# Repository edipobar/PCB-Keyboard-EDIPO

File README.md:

# PCB-Keyboard-EDIPO
Custom Keyboard PCB

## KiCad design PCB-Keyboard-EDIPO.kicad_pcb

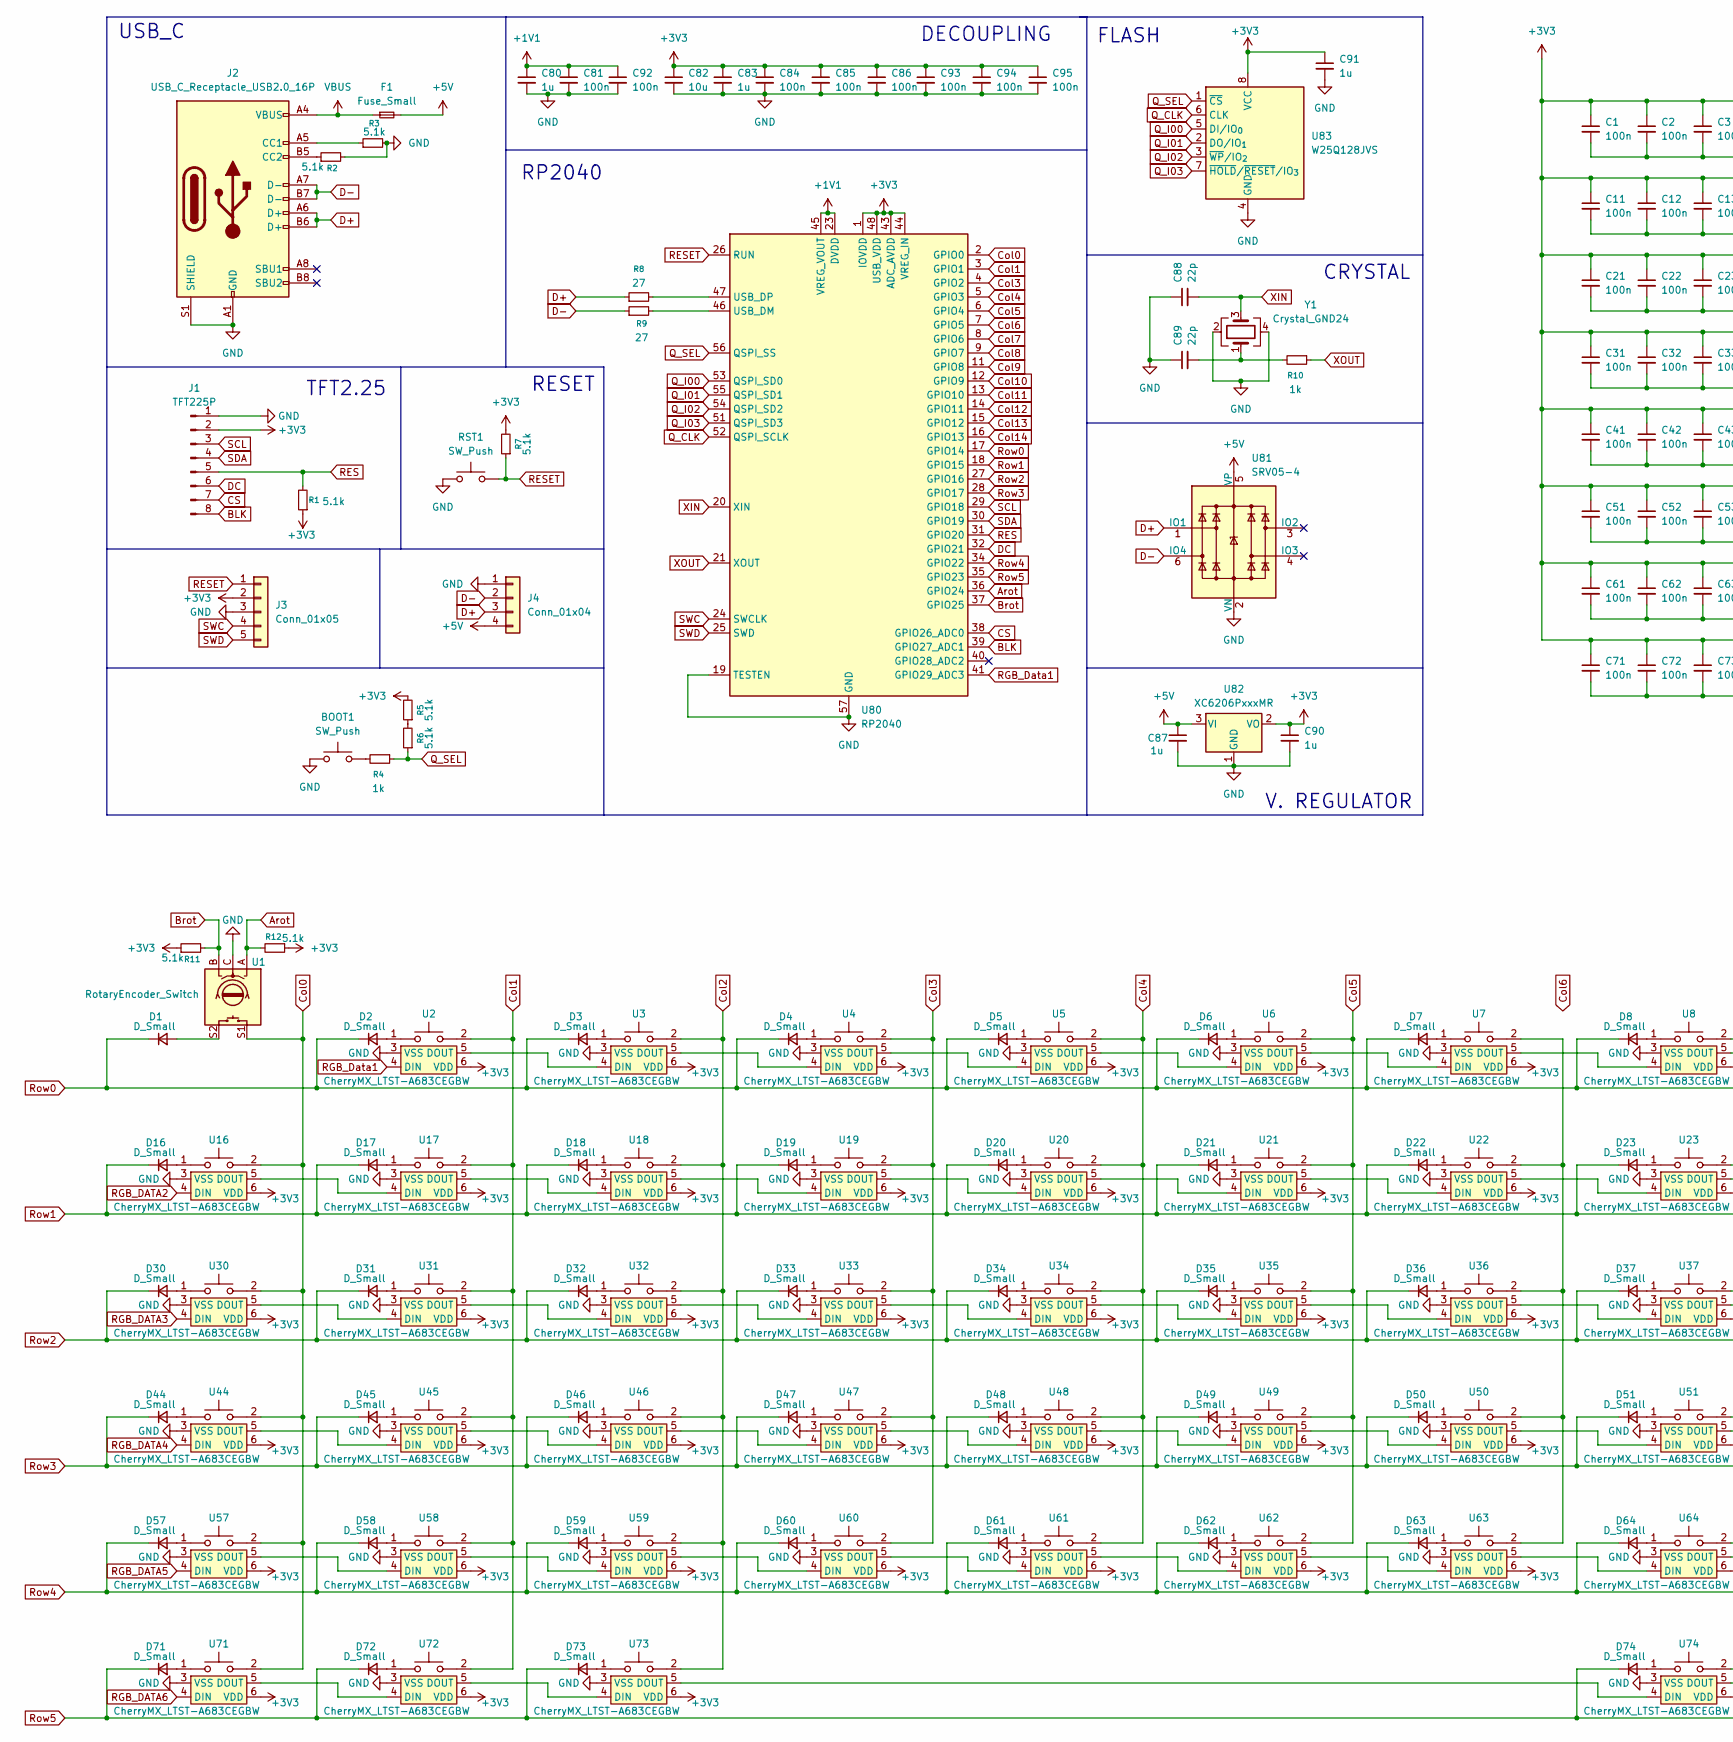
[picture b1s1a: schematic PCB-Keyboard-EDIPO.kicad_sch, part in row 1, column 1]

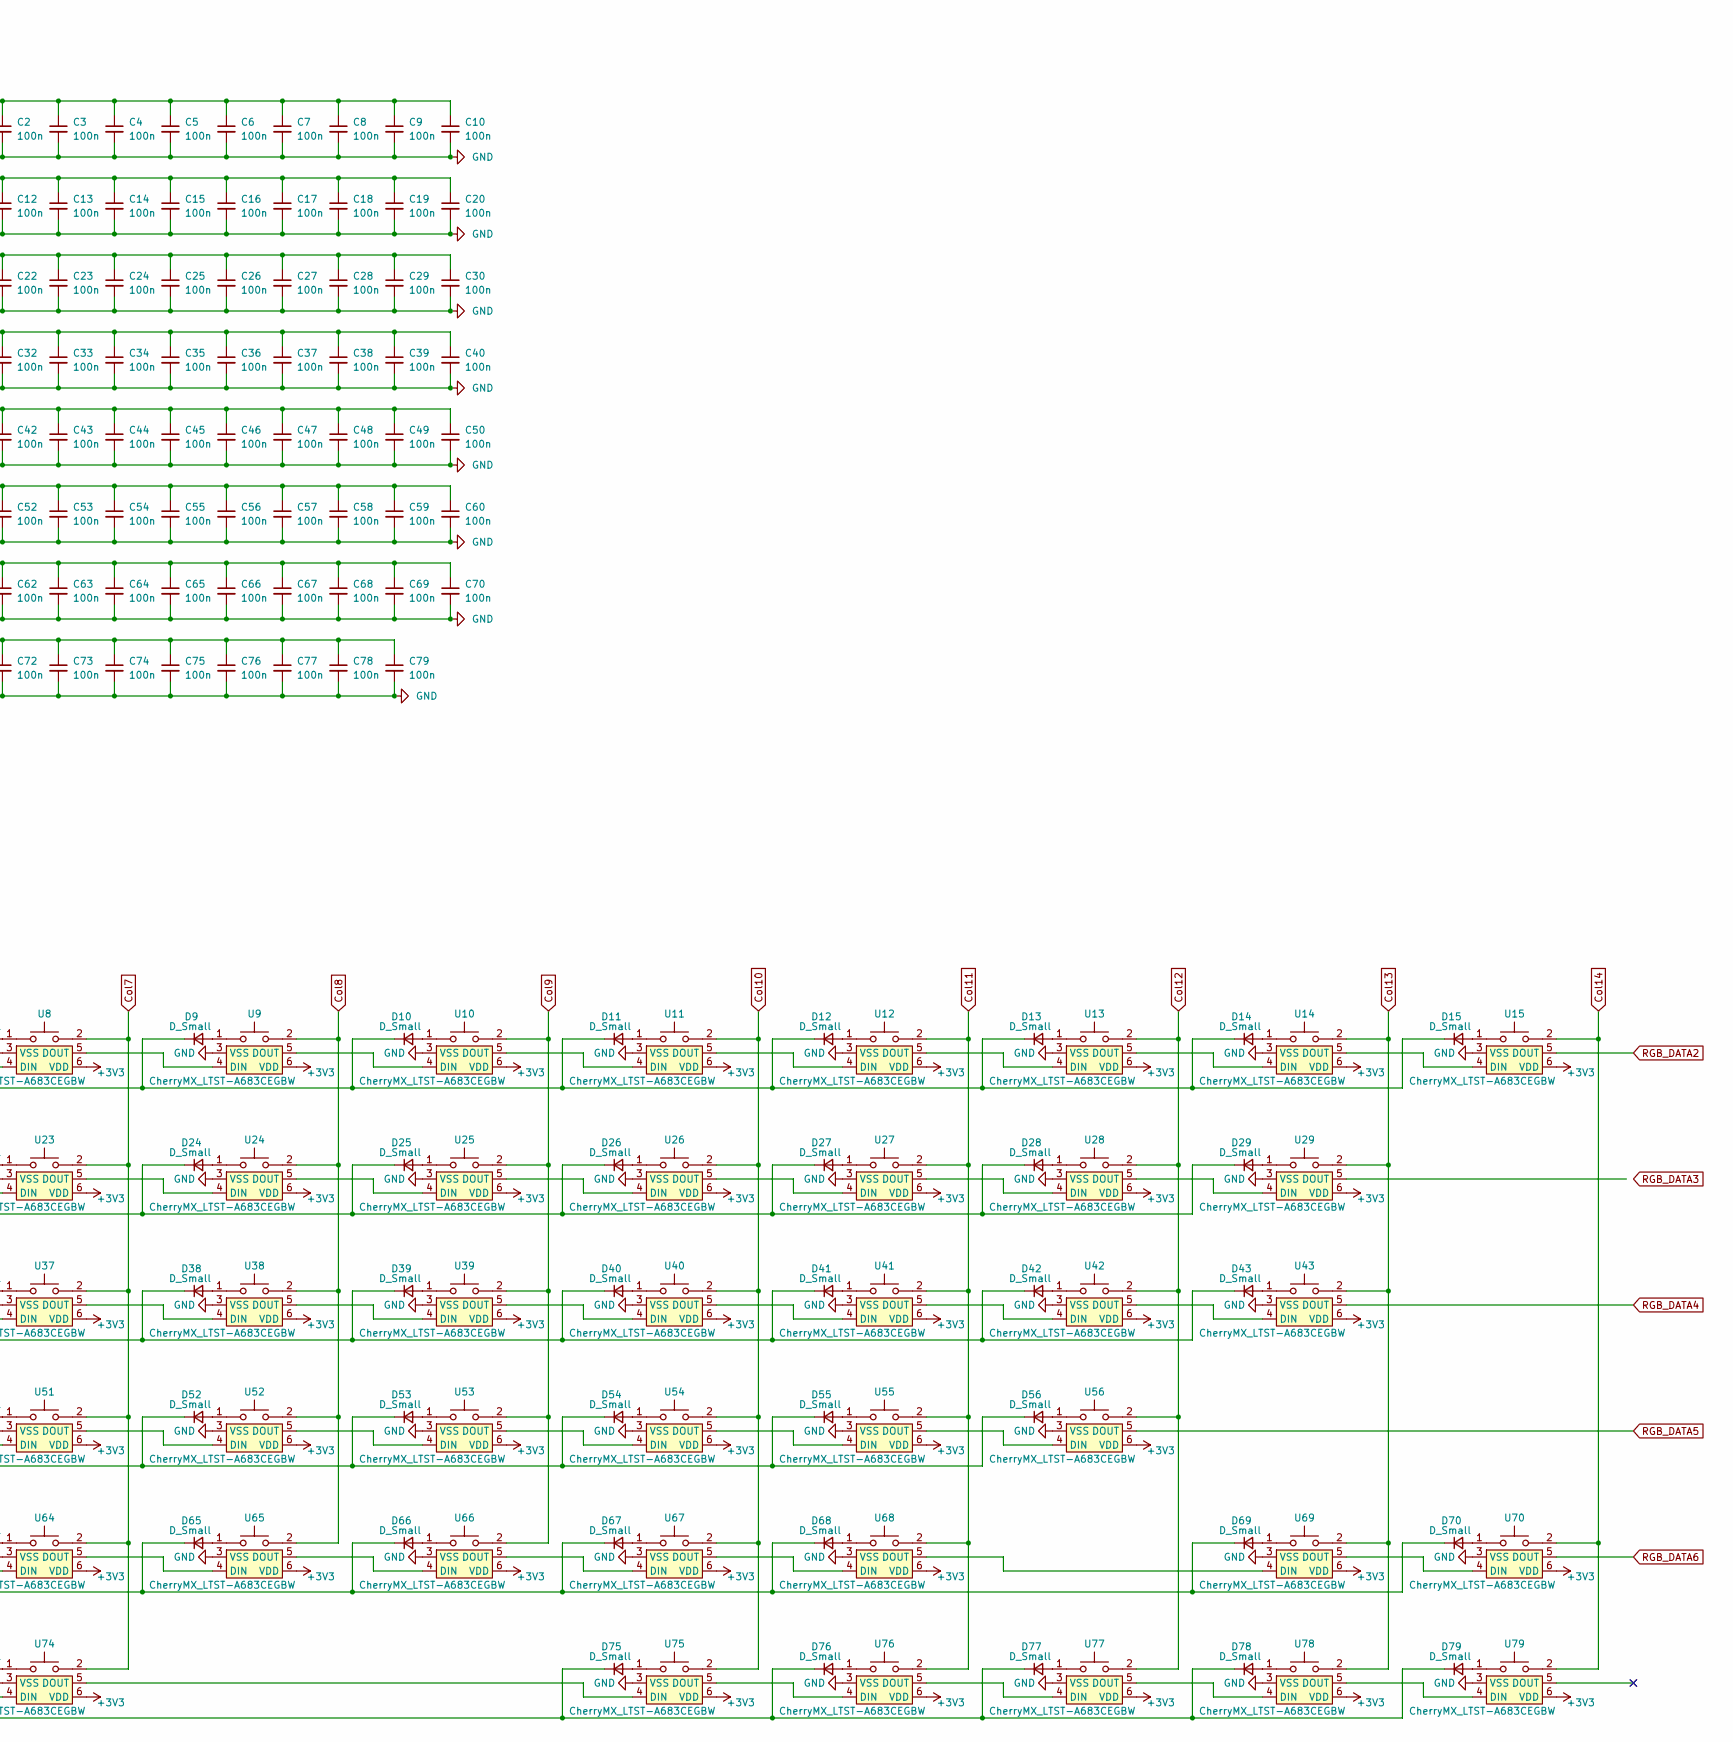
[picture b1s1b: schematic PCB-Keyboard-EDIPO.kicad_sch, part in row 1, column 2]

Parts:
BOOT1: SW_Push; SW_SPST_TL3342
C1, C2, C3, C4, C5, C6, C7, C8, C9, C10, C11, C12, C13, C14, C15, C16, C17, C18, C19, C20, C21, C22, C23, C24, C25, C26, C27, C28, C29, C30, C31, C32, C33, C34, C35, C36, C37, C38, C39, C40, C41, C42, C43, C44, C45, C46, C47, C48, C49, C50, C51, C52, C53, C54, C55, C56, C57, C58, C59, C60, C61, C62, C63, C64, C65, C66, C67, C68, C69, C70, C71, C72, C73, C74, C75, C76, C77, C78, C79, C81, C84, C85, C86, C92, C93, C94, C95: 100n; C_0805_2012Metric_Pad1.18x1.45mm_HandSolder
C80, C83, C87, C90, C91: 1u; C_0805_2012Metric_Pad1.18x1.45mm_HandSolder
C82: 10u; C_0805_2012Metric_Pad1.18x1.45mm_HandSolder
C88, C89: 22p; C_0805_2012Metric_Pad1.18x1.45mm_HandSolder
D1, D2, D3, D4, D5, D6, D7, D8, D9, D10, D11, D12, D13, D14, D15, D16, D17, D18, D19, D20, D21, D22, D23, D24, D25, D26, D27, D28, D29, D30, D31, D32, D33, D34, D35, D36, D37, D38, D39, D40, D41, D42, D43, D44, D45, D46, D47, D48, D49, D50, D51, D52, D53, D54, D55, D56, D57, D58, D59, D60, D61, D62, D63, D64, D65, D66, D67, D68, D69, D70, D71, D72, D73, D74, D75, D76, D77, D78, D79: D_Small; D_SOD-123
F1: Fuse_Small; Fuse_0805_2012Metric_Pad1.15x1.40mm_HandSolder
J1: TFT225P; PinHeader_1x08_P2.54mm_Vertical
J2: USB_C_Receptacle_USB2.0_16P; USB_C_Receptacle_HRO_TYPE-C-31-M-12
J3: Conn_01x05; PinHeader_1x05_P2.54mm_Vertical
J4: Conn_01x04; JST_SH_SM04B-SRSS-TB_1x04-1MP_P1.00mm_Horizontal
R1, R2, R3, R5, R6, R7, R11, R12: 5.1k; R_0805_2012Metric_Pad1.20x1.40mm_HandSolder
R4, R10: 1k; R_0805_2012Metric_Pad1.20x1.40mm_HandSolder
R8, R9: 27; R_0805_2012Metric_Pad1.20x1.40mm_HandSolder
RST1: SW_Push; SW_SPST_TL3342
U1: RotaryEncoder_Switch; RotaryEncoder_Bourns_Horizontal_PEC09-2xxxF-Sxxxx
U2, U3, U4, U5, U6, U7, U8, U9, U10, U11, U12, U13, U14, U15, U16, U17, U18, U19, U20, U21, U22, U23, U24, U25, U26, U27, U28, U31, U32, U33, U34, U35, U36, U37, U38, U39, U40, U41, U42, U45, U46, U47, U48, U49, U50, U51, U52, U53, U54, U55, U58, U59, U60, U61, U62, U63, U64, U65, U66, U67, U69, U70, U76, U77, U78, U79: CherryMX_LTST-A683CEGBW; CherryMX_1.00u_PCB_KailhSocket_LTST-A683CEGBW-HS
U29: CherryMX_LTST-A683CEGBW; CherryMX_2.00u_PCB_KailhSocket_LTST-A683CEGBW-HS
U30, U43, U71, U73: CherryMX_LTST-A683CEGBW; CherryMX_1.50u_PCB_KailhSocket_LTST-A683CEGBW-HS
U44, U68: CherryMX_LTST-A683CEGBW; CherryMX_1.75u_PCB_KailhSocket_LTST-A683CEGBW-HS
U56, U57: CherryMX_LTST-A683CEGBW; CherryMX_2.25u_PCB_KailhSocket_LTST-A683CEGBW-HS
U72, U75: CherryMX_LTST-A683CEGBW; CherryMX_1.25u_PCB_KailhSocket_LTST-A683CEGBW-HS
U74: CherryMX_LTST-A683CEGBW; CherryMX_6.50u_PCB_KailhSocket_LTST-A683CEGBW-HS
U80: RP2040; QFN-56-1EP_7x7mm_P0.4mm_EP3.2x3.2mm
U81: SRV05-4; SOT-23-6-routable
U82: XC6206PxxxMR; SOT-23-3
U83: W25Q128JVS; SOIC-8_5.3x5.3mm_P1.27mm
Y1: Crystal_GND24; Crystal_SMD_3225-4Pin_3.2x2.5mm_HandSoldering

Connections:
+1V1: C80.1, C81.1, C92.1, U80.23 (DVDD), U80.45 (VREG_VOUT), U80.50 (DVDD)
+3V3: C1.1, C2.1, C3.1, C4.1, C5.1, C6.1, C7.1, C8.1, C9.1, C10.1, C11.1, C12.1, C13.1, C14.1, C15.1, C16.1, C17.1, C18.1, C19.1, C20.1, C21.1, C22.1, C23.1, C24.1, C25.1, C26.1, C27.1, C28.1, C29.1, C30.1, C31.1, C32.1, C33.1, C34.1, C35.1, C36.1, C37.1, C38.1, C39.1, C40.1, C41.1, C42.1, C43.1, C44.1, C45.1, C46.1, C47.1, C48.1, C49.1, C50.1, C51.1, C52.1, C53.1, C54.1, C55.1, C56.1, C57.1, C58.1, C59.1, C60.1, C61.1, C62.1, C63.1, C64.1, C65.1, C66.1, C67.1, C68.1, C69.1, C70.1, C71.1, C72.1, C73.1, C74.1, C75.1, C76.1, C77.1, C78.1, C79.1, C82.1, C83.1, C84.1, C85.1, C86.1, C90.1, C91.1, C93.1, C94.1, C95.1, J1.2, J3.2, R1.1, R5.2, R7.2, R11.1, R12.1, U2.6 (VDD), U3.6 (VDD), U4.6 (VDD), U5.6 (VDD), U6.6 (VDD), U7.6 (VDD), U8.6 (VDD), U9.6 (VDD), U10.6 (VDD), U11.6 (VDD), U12.6 (VDD), U13.6 (VDD), U14.6 (VDD), U15.6 (VDD), U16.6 (VDD), U17.6 (VDD), U18.6 (VDD), U19.6 (VDD), U20.6 (VDD), U21.6 (VDD), U22.6 (VDD), U23.6 (VDD), U24.6 (VDD), U25.6 (VDD), U26.6 (VDD), U27.6 (VDD), U28.6 (VDD), U29.6 (VDD), U30.6 (VDD), U31.6 (VDD), U32.6 (VDD), U33.6 (VDD), U34.6 (VDD), U35.6 (VDD), U36.6 (VDD), U37.6 (VDD), U38.6 (VDD), U39.6 (VDD), U40.6 (VDD), U41.6 (VDD), U42.6 (VDD), U43.6 (VDD), U44.6 (VDD), U45.6 (VDD), U46.6 (VDD), U47.6 (VDD), U48.6 (VDD), U49.6 (VDD), U50.6 (VDD), U51.6 (VDD), U52.6 (VDD), U53.6 (VDD), U54.6 (VDD), U55.6 (VDD), U56.6 (VDD), U57.6 (VDD), U58.6 (VDD), U59.6 (VDD), U60.6 (VDD), U61.6 (VDD), U62.6 (VDD), U63.6 (VDD), U64.6 (VDD), U65.6 (VDD), U66.6 (VDD), U67.6 (VDD), U68.6 (VDD), U69.6 (VDD), U70.6 (VDD), U71.6 (VDD), U72.6 (VDD), U73.6 (VDD), U74.6 (VDD), U75.6 (VDD), U76.6 (VDD), U77.6 (VDD), U78.6 (VDD), U79.6 (VDD), U80.1 (IOVDD), U80.10 (IOVDD), U80.22 (IOVDD), U80.33 (IOVDD), U80.42 (IOVDD), U80.43 (ADC_AVDD), U80.44 (VREG_IN), U80.48 (USB_VDD), U80.49 (IOVDD), U82.2 (VO), U83.8 (VCC)
+5V: C87.1, F1.2, J4.4, U81.5 (VP), U82.3 (VI)
Arot: R12.2, U1.A, U80.36 (GPIO24)
BLK: J1.8, U80.39 (GPIO27_ADC1)
Brot: R11.2, U1.B, U80.37 (GPIO25)
CS: J1.7, U80.38 (GPIO26_ADC0)
Col0: U1.S1, U16.2, U30.2, U44.2, U57.2, U71.2, U80.2 (GPIO0)
Col1: U2.2, U17.2, U31.2, U45.2, U58.2, U72.2, U80.3 (GPIO1)
Col2: U3.2, U18.2, U32.2, U46.2, U59.2, U73.2
Col3: U4.2, U19.2, U33.2, U47.2, U60.2, U80.4 (GPIO2)
Col4: U5.2, U20.2, U34.2, U48.2, U61.2, U80.5 (GPIO3)
Col5: U6.2, U21.2, U35.2, U49.2, U62.2, U80.6 (GPIO4)
Col6: U80.7 (GPIO5)
Col7: U8.2, U23.2, U37.2, U51.2, U64.2, U74.2, U80.8 (GPIO6)
Col8: U9.2, U24.2, U38.2, U52.2, U65.2, U80.9 (GPIO7)
Col9: U10.2, U25.2, U39.2, U53.2, U66.2, U80.11 (GPIO8)
Col10: U11.2, U26.2, U40.2, U54.2, U67.2, U75.2, U80.12 (GPIO9)
Col11: U12.2, U27.2, U41.2, U55.2, U68.2, U76.2, U80.13 (GPIO10)
Col12: U13.2, U28.2, U42.2, U56.2, U77.2, U80.14 (GPIO11)
Col13: U14.2, U29.2, U43.2, U69.2, U78.2, U80.15 (GPIO12)
Col14: U15.2, U70.2, U79.2, U80.16 (GPIO13)
D+: J2.A6 (D+), J2.B6 (D+), J4.3, R8.1, U81.1 (IO1)
D-: J2.A7 (D-), J2.B7 (D-), J4.2, R9.1, U81.6 (IO4)
DC: J1.6, U80.32 (GPIO21)
GND: BOOT1.1, C1.2, C2.2, C3.2, C4.2, C5.2, C6.2, C7.2, C8.2, C9.2, C10.2, C11.2, C12.2, C13.2, C14.2, C15.2, C16.2, C17.2, C18.2, C19.2, C20.2, C21.2, C22.2, C23.2, C24.2, C25.2, C26.2, C27.2, C28.2, C29.2, C30.2, C31.2, C32.2, C33.2, C34.2, C35.2, C36.2, C37.2, C38.2, C39.2, C40.2, C41.2, C42.2, C43.2, C44.2, C45.2, C46.2, C47.2, C48.2, C49.2, C50.2, C51.2, C52.2, C53.2, C54.2, C55.2, C56.2, C57.2, C58.2, C59.2, C60.2, C61.2, C62.2, C63.2, C64.2, C65.2, C66.2, C67.2, C68.2, C69.2, C70.2, C71.2, C72.2, C73.2, C74.2, C75.2, C76.2, C77.2, C78.2, C79.2, C80.2, C81.2, C82.2, C83.2, C84.2, C85.2, C86.2, C87.2, C88.1, C89.1, C90.2, C91.2, C92.2, C93.2, C94.2, C95.2, J1.1, J2.A1 (GND), J2.A12 (GND), J2.B1 (GND), J2.B12 (GND), J2.S1 (SHIELD), J3.3, J4.1, R2.2, R3.2, RST1.1, U1.C, U2.3 (VSS), U3.3 (VSS), U4.3 (VSS), U5.3 (VSS), U6.3 (VSS), U7.3 (VSS), U8.3 (VSS), U9.3 (VSS), U10.3 (VSS), U11.3 (VSS), U12.3 (VSS), U13.3 (VSS), U14.3 (VSS), U15.3 (VSS), U16.3 (VSS), U17.3 (VSS), U18.3 (VSS), U19.3 (VSS), U20.3 (VSS), U21.3 (VSS), U22.3 (VSS), U23.3 (VSS), U24.3 (VSS), U25.3 (VSS), U26.3 (VSS), U27.3 (VSS), U28.3 (VSS), U29.3 (VSS), U30.3 (VSS), U31.3 (VSS), U32.3 (VSS), U33.3 (VSS), U34.3 (VSS), U35.3 (VSS), U36.3 (VSS), U37.3 (VSS), U38.3 (VSS), U39.3 (VSS), U40.3 (VSS), U41.3 (VSS), U42.3 (VSS), U43.3 (VSS), U44.3 (VSS), U45.3 (VSS), U46.3 (VSS), U47.3 (VSS), U48.3 (VSS), U49.3 (VSS), U50.3 (VSS), U51.3 (VSS), U52.3 (VSS), U53.3 (VSS), U54.3 (VSS), U55.3 (VSS), U56.3 (VSS), U57.3 (VSS), U58.3 (VSS), U59.3 (VSS), U60.3 (VSS), U61.3 (VSS), U62.3 (VSS), U63.3 (VSS), U64.3 (VSS), U65.3 (VSS), U66.3 (VSS), U67.3 (VSS), U68.3 (VSS), U69.3 (VSS), U70.3 (VSS), U71.3 (VSS), U72.3 (VSS), U73.3 (VSS), U74.3 (VSS), U75.3 (VSS), U76.3 (VSS), U77.3 (VSS), U78.3 (VSS), U79.3 (VSS), U80.19 (TESTEN), U80.57 (GND), U81.2 (VN), U82.1 (GND), U83.4 (GND), Y1.2, Y1.4
unnamed: BOOT1.2, R4.2
unnamed: C89.2, R10.2, Y1.1
unnamed: D1.2 (A), U1.S2
unnamed: D2.2 (A), U2.1
unnamed: D3.2 (A), U3.1
unnamed: D4.2 (A), U4.1
unnamed: D5.2 (A), U5.1
unnamed: D6.2 (A), U6.1
unnamed: D7.2 (A), U7.1
unnamed: D8.2 (A), U8.1
unnamed: D9.2 (A), U9.1
unnamed: D10.2 (A), U10.1
unnamed: D11.2 (A), U11.1
unnamed: D12.2 (A), U12.1
unnamed: D13.2 (A), U13.1
unnamed: D14.2 (A), U14.1
unnamed: D15.2 (A), U15.1
unnamed: D16.2 (A), U16.1
unnamed: D17.2 (A), U17.1
unnamed: D18.2 (A), U18.1
unnamed: D19.2 (A), U19.1
unnamed: D20.2 (A), U20.1
unnamed: D21.2 (A), U21.1
unnamed: D22.2 (A), U22.1
unnamed: D23.2 (A), U23.1
unnamed: D24.2 (A), U24.1
unnamed: D25.2 (A), U25.1
unnamed: D26.2 (A), U26.1
unnamed: D27.2 (A), U27.1
unnamed: D28.2 (A), U28.1
unnamed: D29.2 (A), U29.1
unnamed: D30.2 (A), U30.1
unnamed: D31.2 (A), U31.1
unnamed: D32.2 (A), U32.1
unnamed: D33.2 (A), U33.1
unnamed: D34.2 (A), U34.1
unnamed: D35.2 (A), U35.1
unnamed: D36.2 (A), U36.1
unnamed: D37.2 (A), U37.1
unnamed: D38.2 (A), U38.1
unnamed: D39.2 (A), U39.1
unnamed: D40.2 (A), U40.1
unnamed: D41.2 (A), U41.1
unnamed: D42.2 (A), U42.1
unnamed: D43.2 (A), U43.1
unnamed: D44.2 (A), U44.1
unnamed: D45.2 (A), U45.1
unnamed: D46.2 (A), U46.1
unnamed: D47.2 (A), U47.1
unnamed: D48.2 (A), U48.1
unnamed: D49.2 (A), U49.1
unnamed: D50.2 (A), U50.1
unnamed: D51.2 (A), U51.1
unnamed: D52.2 (A), U52.1
unnamed: D53.2 (A), U53.1
unnamed: D54.2 (A), U54.1
unnamed: D55.2 (A), U55.1
unnamed: D56.2 (A), U56.1
unnamed: D57.2 (A), U57.1
unnamed: D58.2 (A), U58.1
unnamed: D59.2 (A), U59.1
unnamed: D60.2 (A), U60.1
unnamed: D61.2 (A), U61.1
unnamed: D62.2 (A), U62.1
unnamed: D63.2 (A), U63.1
unnamed: D64.2 (A), U64.1
unnamed: D65.2 (A), U65.1
unnamed: D66.2 (A), U66.1
unnamed: D67.2 (A), U67.1
unnamed: D68.2 (A), U68.1
unnamed: D69.2 (A), U69.1
unnamed: D70.2 (A), U70.1
unnamed: D71.2 (A), U71.1
unnamed: D72.2 (A), U72.1
unnamed: D73.2 (A), U73.1
unnamed: D74.2 (A), U74.1
unnamed: D75.2 (A), U75.1
unnamed: D76.2 (A), U76.1
unnamed: D77.2 (A), U77.1
unnamed: D78.2 (A), U78.1
unnamed: D79.2 (A), U79.1
unnamed: J2.A5 (CC1), R3.1
unnamed: J2.B5 (CC2), R2.1
unnamed: R5.1, R6.2
unnamed: U2.5 (DOUT), U3.4 (DIN)
unnamed: U3.5 (DOUT), U4.4 (DIN)
unnamed: U4.5 (DOUT), U5.4 (DIN)
unnamed: U5.5 (DOUT), U6.4 (DIN)
unnamed: U6.5 (DOUT), U7.4 (DIN)
unnamed: U7.5 (DOUT), U8.4 (DIN)
unnamed: U8.5 (DOUT), U9.4 (DIN)
unnamed: U9.5 (DOUT), U10.4 (DIN)
unnamed: U10.5 (DOUT), U11.4 (DIN)
unnamed: U11.5 (DOUT), U12.4 (DIN)
unnamed: U12.5 (DOUT), U13.4 (DIN)
unnamed: U13.5 (DOUT), U14.4 (DIN)
unnamed: U14.5 (DOUT), U15.4 (DIN)
unnamed: U16.5 (DOUT), U17.4 (DIN)
unnamed: U17.5 (DOUT), U18.4 (DIN)
unnamed: U18.5 (DOUT), U19.4 (DIN)
unnamed: U19.5 (DOUT), U20.4 (DIN)
unnamed: U20.5 (DOUT), U21.4 (DIN)
unnamed: U21.5 (DOUT), U22.4 (DIN)
unnamed: U22.5 (DOUT), U23.4 (DIN)
unnamed: U7.2, U22.2, U36.2, U50.2, U63.2
unnamed: U23.5 (DOUT), U24.4 (DIN)
unnamed: U24.5 (DOUT), U25.4 (DIN)
unnamed: U25.5 (DOUT), U26.4 (DIN)
unnamed: U26.5 (DOUT), U27.4 (DIN)
unnamed: U27.5 (DOUT), U28.4 (DIN)
unnamed: U28.5 (DOUT), U29.4 (DIN)
unnamed: U30.5 (DOUT), U31.4 (DIN)
unnamed: U31.5 (DOUT), U32.4 (DIN)
unnamed: U32.5 (DOUT), U33.4 (DIN)
unnamed: U33.5 (DOUT), U34.4 (DIN)
unnamed: U34.5 (DOUT), U35.4 (DIN)
unnamed: U35.5 (DOUT), U36.4 (DIN)
unnamed: U36.5 (DOUT), U37.4 (DIN)
unnamed: U37.5 (DOUT), U38.4 (DIN)
unnamed: U38.5 (DOUT), U39.4 (DIN)
unnamed: U39.5 (DOUT), U40.4 (DIN)
unnamed: U40.5 (DOUT), U41.4 (DIN)
unnamed: U41.5 (DOUT), U42.4 (DIN)
unnamed: U42.5 (DOUT), U43.4 (DIN)
unnamed: U44.5 (DOUT), U45.4 (DIN)
unnamed: U45.5 (DOUT), U46.4 (DIN)
unnamed: U46.5 (DOUT), U47.4 (DIN)
unnamed: U47.5 (DOUT), U48.4 (DIN)
unnamed: U48.5 (DOUT), U49.4 (DIN)
unnamed: U49.5 (DOUT), U50.4 (DIN)
unnamed: U50.5 (DOUT), U51.4 (DIN)
unnamed: U51.5 (DOUT), U52.4 (DIN)
unnamed: U52.5 (DOUT), U53.4 (DIN)
unnamed: U53.5 (DOUT), U54.4 (DIN)
unnamed: U54.5 (DOUT), U55.4 (DIN)
unnamed: U55.5 (DOUT), U56.4 (DIN)
unnamed: U57.5 (DOUT), U58.4 (DIN)
unnamed: U58.5 (DOUT), U59.4 (DIN)
unnamed: U59.5 (DOUT), U60.4 (DIN)
unnamed: U60.5 (DOUT), U61.4 (DIN)
unnamed: U61.5 (DOUT), U62.4 (DIN)
unnamed: U62.5 (DOUT), U63.4 (DIN)
unnamed: U63.5 (DOUT), U64.4 (DIN)
unnamed: U64.5 (DOUT), U65.4 (DIN)
unnamed: U65.5 (DOUT), U66.4 (DIN)
unnamed: U66.5 (DOUT), U67.4 (DIN)
unnamed: U67.5 (DOUT), U68.4 (DIN)
unnamed: U68.5 (DOUT), U69.4 (DIN)
unnamed: U69.5 (DOUT), U70.4 (DIN)
unnamed: U71.5 (DOUT), U72.4 (DIN)
unnamed: U72.5 (DOUT), U73.4 (DIN)
unnamed: U73.5 (DOUT), U74.4 (DIN)
unnamed: U74.5 (DOUT), U75.4 (DIN)
unnamed: U75.5 (DOUT), U76.4 (DIN)
unnamed: U76.5 (DOUT), U77.4 (DIN)
unnamed: U77.5 (DOUT), U78.4 (DIN)
unnamed: U78.5 (DOUT), U79.4 (DIN)
unnamed: R9.2, U80.46 (USB_DM)
unnamed: R8.2, U80.47 (USB_DP)
Q_CLK: U80.52 (QSPI_SCLK), U83.6 (CLK)
Q_I00: U80.53 (QSPI_SD0), U83.5 (DI/IO_{0})
Q_I01: U80.55 (QSPI_SD1), U83.2 (DO/IO_{1})
Q_I02: U80.54 (QSPI_SD2), U83.3 (~WP/IO_{2})
Q_I03: U80.51 (QSPI_SD3), U83.7 (~HOLD/~RESET/IO_{3})
Q_SEL: R4.1, R6.1, U80.56 (QSPI_SS), U83.1 (~CS)
RES: J1.5, R1.2, U80.31 (GPIO20)
RESET: J3.1, R7.1, RST1.2, U80.26 (RUN)
RGB_DATA2: U15.5 (DOUT), U16.4 (DIN)
RGB_DATA3: U30.4 (DIN)
RGB_DATA4: U43.5 (DOUT), U44.4 (DIN)
RGB_DATA5: U56.5 (DOUT), U57.4 (DIN)
RGB_DATA6: U70.5 (DOUT), U71.4 (DIN)
RGB_Data1: U2.4 (DIN), U80.41 (GPIO29_ADC3)
Row0: D1.1 (K), D2.1 (K), D3.1 (K), D4.1 (K), D5.1 (K), D6.1 (K), D7.1 (K), D8.1 (K), D9.1 (K), D10.1 (K), D11.1 (K), D12.1 (K), D13.1 (K), D14.1 (K), D15.1 (K), U80.17 (GPIO14)
Row1: D16.1 (K), D17.1 (K), D18.1 (K), D19.1 (K), D20.1 (K), D21.1 (K), D22.1 (K), D23.1 (K), D24.1 (K), D25.1 (K), D26.1 (K), D27.1 (K), D28.1 (K), D29.1 (K), U80.18 (GPIO15)
Row2: D30.1 (K), D31.1 (K), D32.1 (K), D33.1 (K), D34.1 (K), D35.1 (K), D36.1 (K), D37.1 (K), D38.1 (K), D39.1 (K), D40.1 (K), D41.1 (K), D42.1 (K), D43.1 (K), U80.27 (GPIO16)
Row3: D44.1 (K), D45.1 (K), D46.1 (K), D47.1 (K), D48.1 (K), D49.1 (K), D50.1 (K), D51.1 (K), D52.1 (K), D53.1 (K), D54.1 (K), D55.1 (K), D56.1 (K), U80.28 (GPIO17)
Row4: D57.1 (K), D58.1 (K), D59.1 (K), D60.1 (K), D61.1 (K), D62.1 (K), D63.1 (K), D64.1 (K), D65.1 (K), D66.1 (K), D67.1 (K), D68.1 (K), D69.1 (K), D70.1 (K), U80.34 (GPIO22)
Row5: D71.1 (K), D72.1 (K), D73.1 (K), D74.1 (K), D75.1 (K), D76.1 (K), D77.1 (K), D78.1 (K), D79.1 (K), U80.35 (GPIO23)
SCL: J1.3, U80.29 (GPIO18)
SDA: J1.4, U80.30 (GPIO19)
SWC: J3.4, U80.24 (SWCLK)
SWD: J3.5, U80.25 (SWD)
VBUS: F1.1, J2.A4 (VBUS), J2.A9 (VBUS), J2.B4 (VBUS), J2.B9 (VBUS)
XIN: C88.2, U80.20 (XIN), Y1.3
XOUT: R10.1, U80.21 (XOUT)

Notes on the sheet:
V. REGULATOR
CRYSTAL
DECOUPLING
FLASH
USB_C
RP2040
RESET
TFT2.25

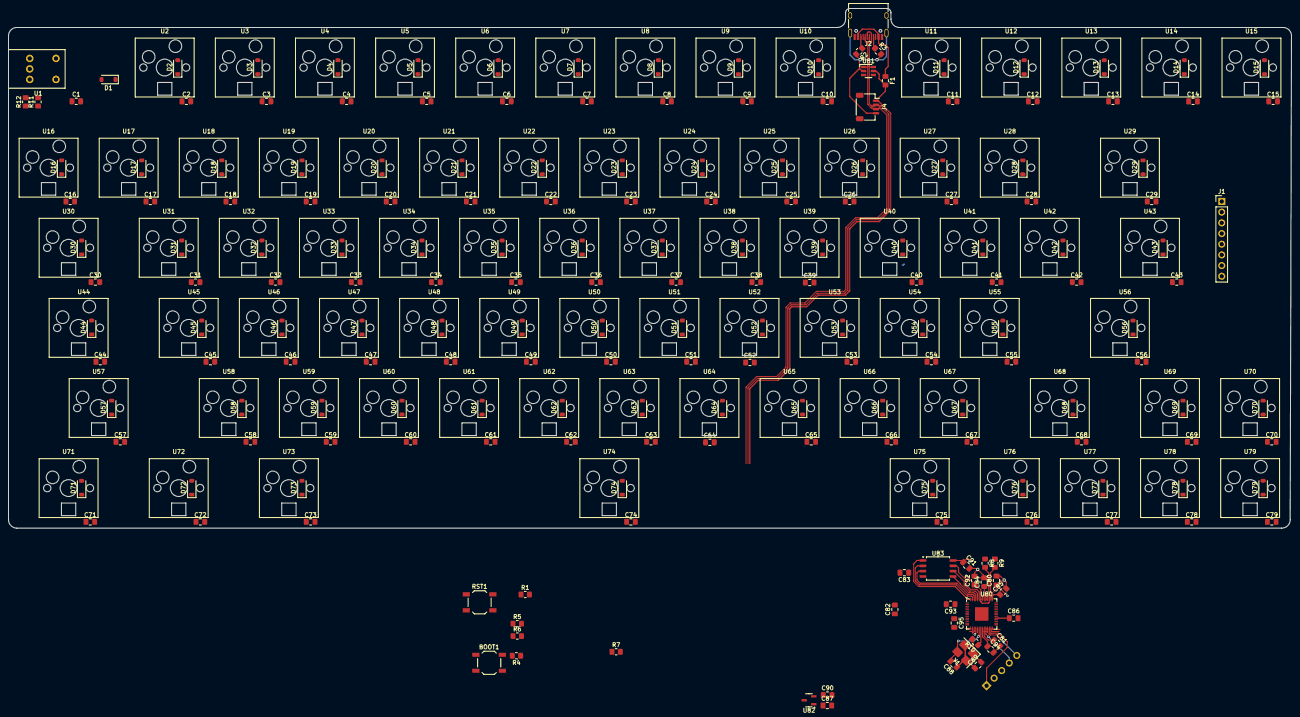
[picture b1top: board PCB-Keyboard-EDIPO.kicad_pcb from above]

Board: 2 copper layers, 305.1 x 123.6 mm, 277 parts (1 on the bottom side), 210 nets.

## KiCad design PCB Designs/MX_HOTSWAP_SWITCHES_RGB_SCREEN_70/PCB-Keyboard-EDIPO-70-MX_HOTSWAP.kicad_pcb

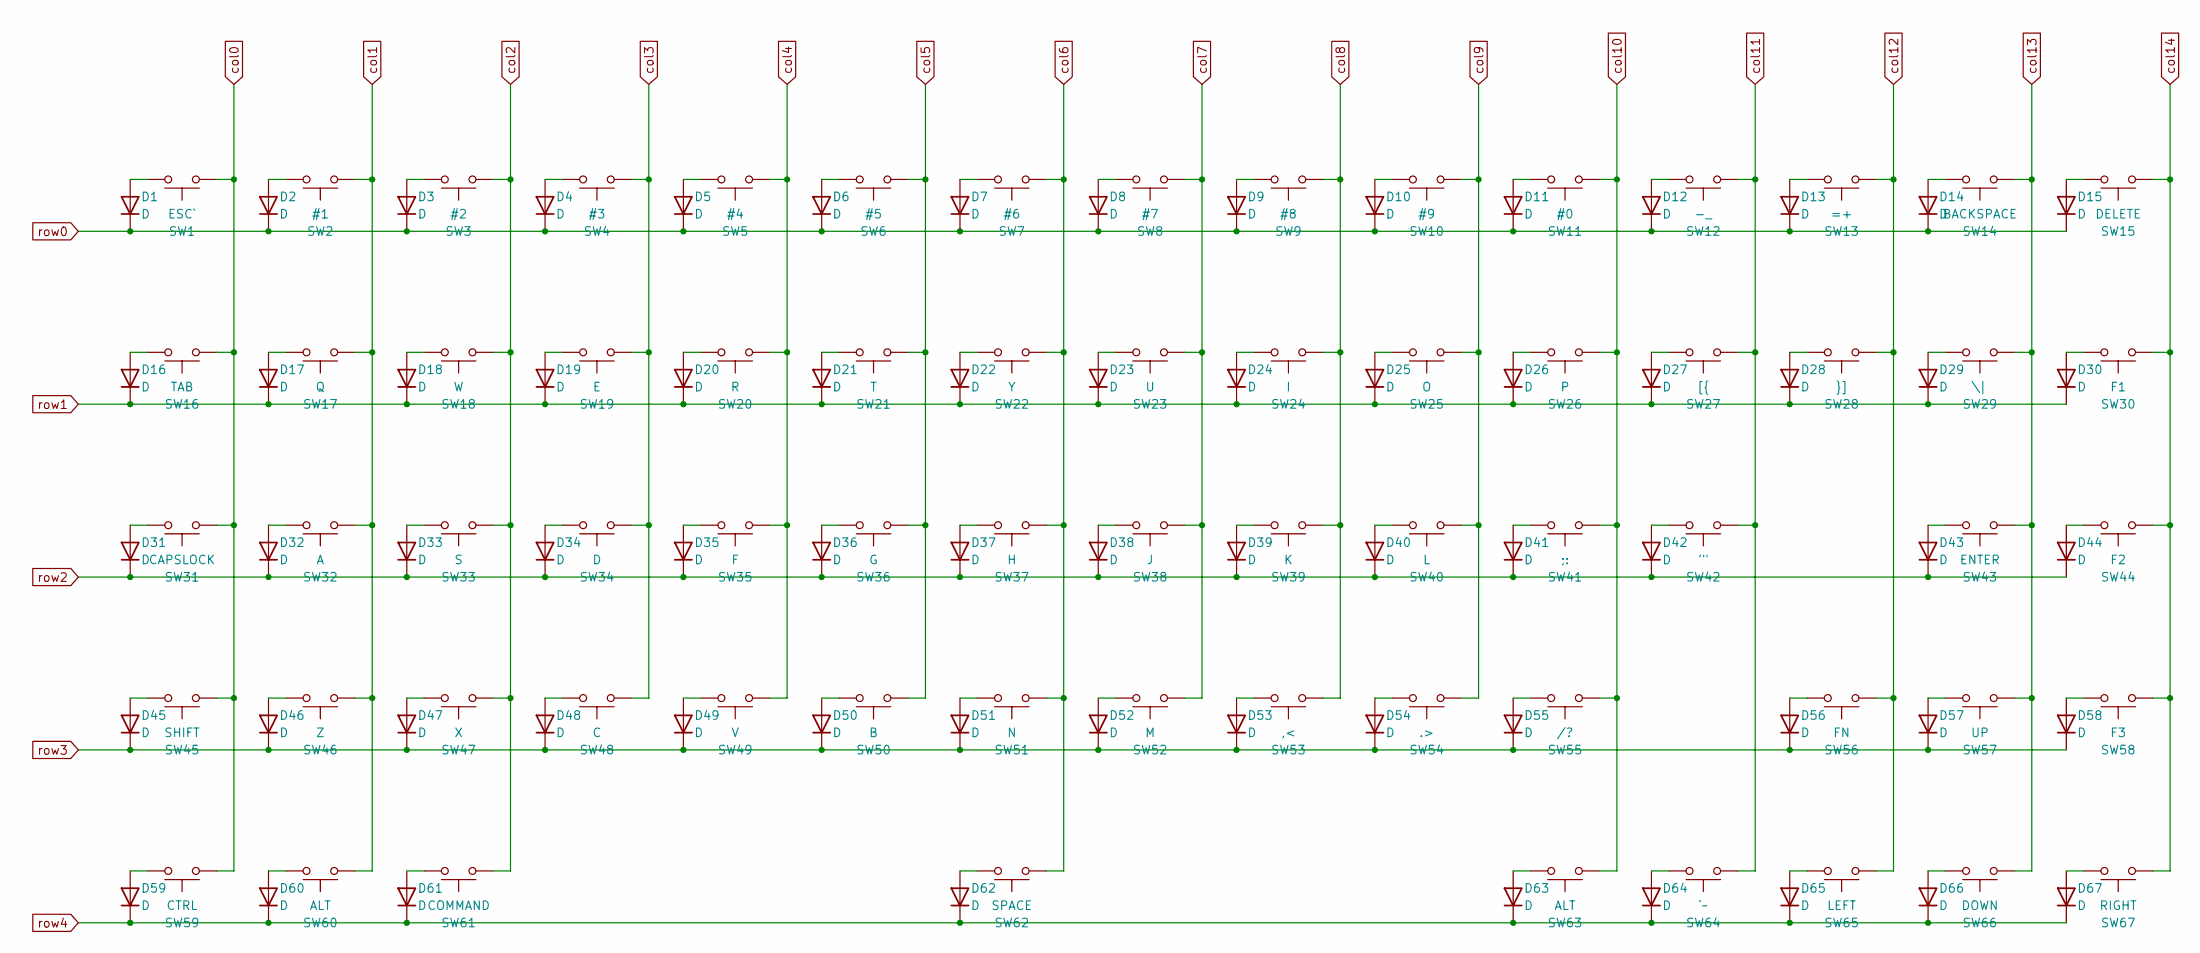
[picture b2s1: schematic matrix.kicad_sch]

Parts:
D1, D2, D3, D4, D5, D6, D7, D8, D9, D10, D11, D12, D13, D14, D15, D16, D17, D18, D19, D20, D21, D22, D23, D24, D25, D26, D27, D28, D29, D30, D31, D32, D33, D34, D35, D36, D37, D38, D39, D40, D41, D42, D43, D44, D45, D46, D47, D48, D49, D50, D51, D52, D53, D54, D55, D56, D57, D58, D59, D60, D61, D62, D63, D64, D65, D66, D67: D; D_SOD-123
SW1: ESC`; ALPS-1U
SW2: #1; ALPS-1U
SW3: #2; ALPS-1U
SW4: #3; ALPS-1U
SW5: #4; ALPS-1U
SW6: #5; ALPS-1U
SW7: #6; ALPS-1U
SW8: #7; ALPS-1U
SW9: #8; ALPS-1U
SW10: #9; ALPS-1U
SW11: #0; ALPS-1U
SW12: -_; ALPS-1U
SW13: =+; ALPS-1U
SW14: BACKSPACE; ALPS-2U
SW15: DELETE; ALPS-1U
SW16: TAB; ALPS-1.5U
SW17: Q; ALPS-1U
SW18: W; ALPS-1U
SW19: E; ALPS-1U
SW20: R; ALPS-1U
SW21: T; ALPS-1U
SW22: Y; ALPS-1U
SW23: U; ALPS-1U
SW24: I; ALPS-1U
SW25: O; ALPS-1U
SW26: P; ALPS-1U
SW27: [{; ALPS-1U
SW28: }]; ALPS-1U
SW29: \|; ALPS-1.5U
SW30: F1; ALPS-1U
SW31: CAPSLOCK; ALPS-1.75U
SW32: A; ALPS-1U
SW33: S; ALPS-1U
SW34: D; ALPS-1U
SW35: F; ALPS-1U
SW36: G; ALPS-1U
SW37: H; ALPS-1U
SW38: J; ALPS-1U
SW39: K; ALPS-1U
SW40: L; ALPS-1U
SW41: ;:; ALPS-1U
SW42: '"; ALPS-1U
SW43: ENTER; ALPS-2.25U
SW44: F2; ALPS-1U
SW45: SHIFT; ALPS-2.25U
SW46: Z; ALPS-1U
SW47: X; ALPS-1U
SW48: C; ALPS-1U
SW49: V; ALPS-1U
SW50: B; ALPS-1U
SW51: N; ALPS-1U
SW52: M; ALPS-1U
SW53: ,<; ALPS-1U
SW54: .>; ALPS-1U
SW55: /?; ALPS-1U
SW56: FN; ALPS-1.75U
SW57: UP; ALPS-1U
SW58: F3; ALPS-1U
SW59: CTRL; ALPS-1.5U
SW60, SW63: ALT; ALPS-1.25U
SW61: COMMAND; ALPS-1.5U
SW62: SPACE; ALPS-6.5U
SW64: `~; ALPS-1U
SW65: LEFT; ALPS-1U
SW66: DOWN; ALPS-1U
SW67: RIGHT; ALPS-1U

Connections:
unnamed: D1.2 (A), SW1.2
unnamed: D2.2 (A), SW2.2
unnamed: D3.2 (A), SW3.2
unnamed: D4.2 (A), SW4.2
unnamed: D5.2 (A), SW5.2
unnamed: D6.2 (A), SW6.2
unnamed: D7.2 (A), SW7.2
unnamed: D8.2 (A), SW8.2
unnamed: D9.2 (A), SW9.2
unnamed: D10.2 (A), SW10.2
unnamed: D11.2 (A), SW11.2
unnamed: D12.2 (A), SW12.2
unnamed: D13.2 (A), SW13.2
unnamed: D14.2 (A), SW14.2
unnamed: D15.2 (A), SW15.2
unnamed: D16.2 (A), SW16.2
unnamed: D17.2 (A), SW17.2
unnamed: D18.2 (A), SW18.2
unnamed: D19.2 (A), SW19.2
unnamed: D20.2 (A), SW20.2
unnamed: D21.2 (A), SW21.2
unnamed: D22.2 (A), SW22.2
unnamed: D23.2 (A), SW23.2
unnamed: D24.2 (A), SW24.2
unnamed: D25.2 (A), SW25.2
unnamed: D26.2 (A), SW26.2
unnamed: D27.2 (A), SW27.2
unnamed: D28.2 (A), SW28.2
unnamed: D29.2 (A), SW29.2
unnamed: D30.2 (A), SW30.2
unnamed: D31.2 (A), SW31.2
unnamed: D32.2 (A), SW32.2
unnamed: D33.2 (A), SW33.2
unnamed: D34.2 (A), SW34.2
unnamed: D35.2 (A), SW35.2
unnamed: D36.2 (A), SW36.2
unnamed: D37.2 (A), SW37.2
unnamed: D38.2 (A), SW38.2
unnamed: D39.2 (A), SW39.2
unnamed: D40.2 (A), SW40.2
unnamed: D41.2 (A), SW41.2
unnamed: D42.2 (A), SW42.2
unnamed: D43.2 (A), SW43.2
unnamed: D44.2 (A), SW44.2
unnamed: D45.2 (A), SW45.2
unnamed: D46.2 (A), SW46.2
unnamed: D47.2 (A), SW47.2
unnamed: D48.2 (A), SW48.2
unnamed: D49.2 (A), SW49.2
unnamed: D50.2 (A), SW50.2
unnamed: D51.2 (A), SW51.2
unnamed: D52.2 (A), SW52.2
unnamed: D53.2 (A), SW53.2
unnamed: D54.2 (A), SW54.2
unnamed: D55.2 (A), SW55.2
unnamed: D56.2 (A), SW56.2
unnamed: D57.2 (A), SW57.2
unnamed: D58.2 (A), SW58.2
unnamed: D59.2 (A), SW59.2
unnamed: D60.2 (A), SW60.2
unnamed: D61.2 (A), SW61.2
unnamed: D62.2 (A), SW62.2
unnamed: D63.2 (A), SW63.2
unnamed: D64.2 (A), SW64.2
unnamed: D65.2 (A), SW65.2
unnamed: D66.2 (A), SW66.2
unnamed: D67.2 (A), SW67.2
col0: SW1.1, SW16.1, SW31.1, SW45.1, SW59.1; also elsewhere on the board
col1: SW2.1, SW17.1, SW32.1, SW46.1, SW60.1; also elsewhere on the board
col2: SW3.1, SW18.1, SW33.1, SW47.1, SW61.1; also elsewhere on the board
col3: SW4.1, SW19.1, SW34.1, SW48.1; also elsewhere on the board
col4: SW5.1, SW20.1, SW35.1, SW49.1; also elsewhere on the board
col5: SW6.1, SW21.1, SW36.1, SW50.1; also elsewhere on the board
col6: SW7.1, SW22.1, SW37.1, SW51.1, SW62.1; also elsewhere on the board
col7: SW8.1, SW23.1, SW38.1, SW52.1; also elsewhere on the board
col8: SW9.1, SW24.1, SW39.1, SW53.1; also elsewhere on the board
col9: SW10.1, SW25.1, SW40.1, SW54.1; also elsewhere on the board
col10: SW11.1, SW26.1, SW41.1, SW55.1, SW63.1; also elsewhere on the board
col11: SW12.1, SW27.1, SW42.1, SW64.1; also elsewhere on the board
col12: SW13.1, SW28.1, SW56.1, SW65.1; also elsewhere on the board
col13: SW14.1, SW29.1, SW43.1, SW57.1, SW66.1; also elsewhere on the board
col14: SW15.1, SW30.1, SW44.1, SW58.1, SW67.1; also elsewhere on the board
row0: D1.1 (K), D2.1 (K), D3.1 (K), D4.1 (K), D5.1 (K), D6.1 (K), D7.1 (K), D8.1 (K), D9.1 (K), D10.1 (K), D11.1 (K), D12.1 (K), D13.1 (K), D14.1 (K), D15.1 (K); also elsewhere on the board
row1: D16.1 (K), D17.1 (K), D18.1 (K), D19.1 (K), D20.1 (K), D21.1 (K), D22.1 (K), D23.1 (K), D24.1 (K), D25.1 (K), D26.1 (K), D27.1 (K), D28.1 (K), D29.1 (K), D30.1 (K); also elsewhere on the board
row2: D31.1 (K), D32.1 (K), D33.1 (K), D34.1 (K), D35.1 (K), D36.1 (K), D37.1 (K), D38.1 (K), D39.1 (K), D40.1 (K), D41.1 (K), D42.1 (K), D43.1 (K), D44.1 (K); also elsewhere on the board
row3: D45.1 (K), D46.1 (K), D47.1 (K), D48.1 (K), D49.1 (K), D50.1 (K), D51.1 (K), D52.1 (K), D53.1 (K), D54.1 (K), D55.1 (K), D56.1 (K), D57.1 (K), D58.1 (K); also elsewhere on the board
row4: D59.1 (K), D60.1 (K), D61.1 (K), D62.1 (K), D63.1 (K), D64.1 (K), D65.1 (K), D66.1 (K), D67.1 (K); also elsewhere on the board

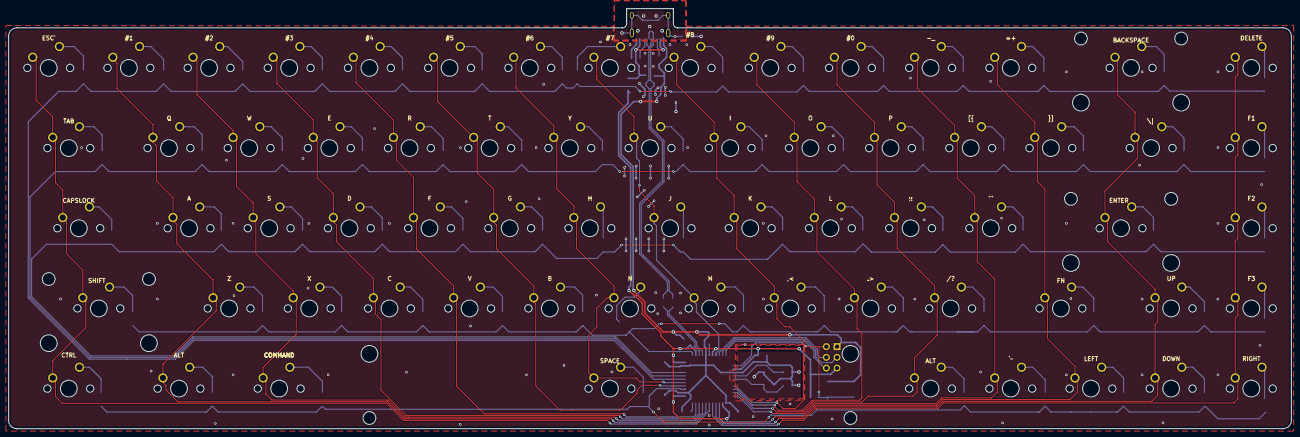
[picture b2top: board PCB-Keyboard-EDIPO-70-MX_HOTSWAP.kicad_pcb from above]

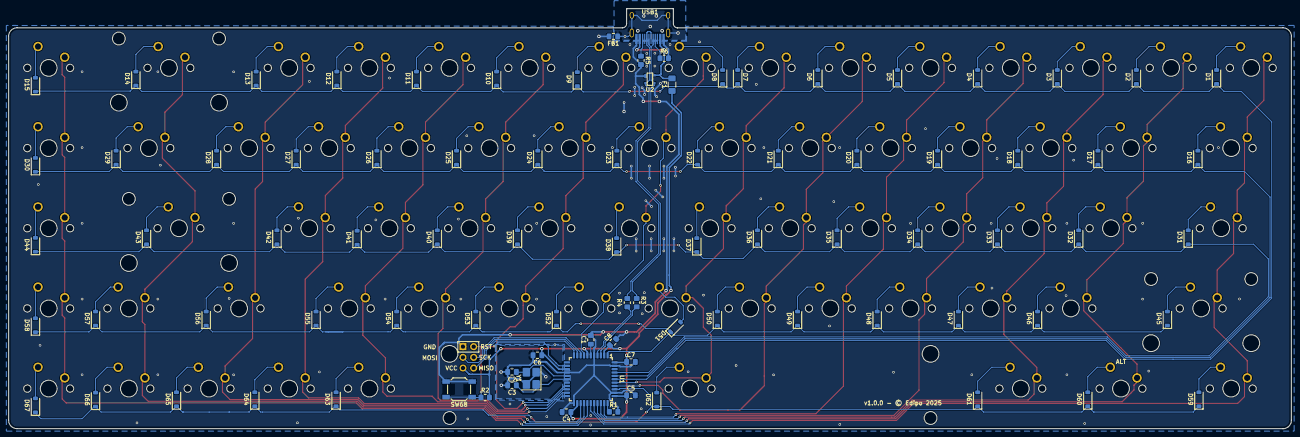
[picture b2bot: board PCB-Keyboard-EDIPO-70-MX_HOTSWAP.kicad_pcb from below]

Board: 2 copper layers, 304.8 x 99.8 mm, 156 parts (89 on the bottom side), 105 nets.

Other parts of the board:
C1: 1u; C_0805_2012Metric_Pad1.18x1.45mm_HandSolder
C2, C3: 22p; C_0805_2012Metric_Pad1.18x1.45mm_HandSolder
C4, C5, C6, C7: 0.1u; C_0805_2012Metric_Pad1.18x1.45mm_HandSolder
C8: 10u; C_0805_2012Metric_Pad1.18x1.45mm_HandSolder
F1: 500m; Fuse_1206_3216Metric_Pad1.42x1.75mm_HandSolder
FB1: 60@100MHz; L_0805_2012Metric_Pad1.15x1.40mm_HandSolder
J1: AVR-ISP-6; Reset_Pretty-Mask
R1, R2: 10k; R_0805_2012Metric_Pad1.20x1.40mm_HandSolder
R3, R4: 22; R_0805_2012Metric_Pad1.20x1.40mm_HandSolder
R5, R6: 5.1k; R_0805_2012Metric_Pad1.20x1.40mm_HandSolder
SW68: SW_Push_Reset; SW_SPST_SKQG_WithStem
U1: ATmega32U4-A; TQFP-44_10x10mm_P0.8mm
U2: PRTR5V0U2X; SOT143B
USB1: HRO-TYPE-C-31-M-12; HRO-TYPE-C-31-M-12-HandSoldering
Y1: XTAL; Crystal_SMD_3225-4Pin_3.2x2.5mm_HandSoldering

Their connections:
+5V: C4.1, C5.1, C6.1, C7.1, C8.1, F1.1, J1.2 (VCC), R2.2, U1.2 (UVCC), U1.7 (VBUS), U1.14 (VCC), U1.24 (AVCC), U1.34 (VCC), U1.44 (AVCC)
D+: R4.2, U1.4 (D+)
D-: R3.2, U1.3 (D-)
DN: R3.1, U2.3 (IO2), USB1.5 (DN2), USB1.7 (DN1)
DP: R4.1, U2.2 (IO1), USB1.6 (DP1), USB1.8 (DP2)
Earth: FB1.1, USB1.13 (SHIELD)
GND: C1.2, C2.2, C3.2, C4.2, C5.2, C6.2, C7.2, C8.2, FB1.2, J1.6 (GND), R1.2, R5.2, R6.2, SW68.2, U1.5 (UGND), U1.15 (GND), U1.23 (GND), U1.35 (GND), U1.43 (GND), U2.1 (GND), USB1.1 (GND), USB1.12 (GND), Y1.2, Y1.4
MISO: J1.1 (MISO), U1.11 (PB3)
MOSI: J1.4 (MOSI), U1.10 (PB2)
unnamed: C1.1, U1.6 (UCAP)
unnamed: R1.1, U1.33 (~HWB/PE2)
unnamed: R6.1, USB1.4 (CC1)
unnamed: R5.1, USB1.10 (CC2)
RESET: J1.5 (~RST), R2.1, SW68.1, U1.13 (~RESET)
SCK: J1.3 (SCK), U1.9 (PB1)
VCC: F1.2, U2.4 (VCC), USB1.2 (VBUS), USB1.11 (VBUS)
XTAL1: C3.1, U1.17 (XTAL1), Y1.1
XTAL2: C2.1, U1.16 (XTAL2), Y1.3
col0: U1.28 (PB4); also elsewhere on the board
col1: U1.29 (PB5); also elsewhere on the board
col2: U1.30 (PB6); also elsewhere on the board
col3: U1.31 (PC6); also elsewhere on the board
col4: U1.32 (PC7); also elsewhere on the board
col5: U1.37 (PF6); also elsewhere on the board
col6: U1.38 (PF5); also elsewhere on the board
col7: U1.8 (PB0); also elsewhere on the board
col8: U1.19 (PD1); also elsewhere on the board
col9: U1.20 (PD2); also elsewhere on the board
col10: U1.21 (PD3); also elsewhere on the board
col11: U1.22 (PD5); also elsewhere on the board
col12: U1.25 (PD4); also elsewhere on the board
col13: U1.26 (PD6); also elsewhere on the board
col14: U1.27 (PD7); also elsewhere on the board
row0: U1.39 (PF4); also elsewhere on the board
row1: U1.40 (PF1); also elsewhere on the board
row2: U1.41 (PF0); also elsewhere on the board
row3: U1.1 (PE6); also elsewhere on the board
row4: U1.36 (PF7); also elsewhere on the board

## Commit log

2025-07-25 Initialize Project
2025-07-25 Libraries
2025-07-25 MCU Edits
2025-07-29 Part 1
    MCU, USB Port, Switch Matrix
2025-07-30 Matrix Strart
2025-07-30 Matrix Design and slight keycap config
2025-07-30 Matrix Design Done
    still need to assign footprints
2025-07-31 Footprints Added
2025-07-31 PCB Started
    need to properly locate pcb components
2025-07-31 Alight PCB Matrix
2025-07-31 Switch (SW_PUSH) Orientation Flip
    rotated SW_PUSH in schematic to align with tutorial
2025-07-31 PCB Component Movement 1
2025-07-31 Part 3 Finished
    Extra decoupling capacitor warning (I changed it font to make it easily noticable)
2025-08-02 Wires
2025-08-04 Routing 1
2025-08-04 Rough Routing Completed
    Must now fix errors if any
2025-08-05 Routed 2
2025-08-05 Logo
2025-08-06 Ground Pour 1
2025-08-06 Via Stitching to ground
2025-08-07 PCB v1.0.1
2025-08-10 zoning
2025-08-11 Converted to MX Only
2025-08-18 Finished PCB
2025-08-18 Fixed Last Traces
2025-08-28 File Reform
    Organizing file for more PCB designs
2025-09-01 new sketch
2025-09-02 new schema
2025-09-10 pcb keyboard 2
2025-09-10 PCB3
2025-09-22 update to rp20 keyboard pcb

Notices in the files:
PCB Designs/MX_HOTSWAP_SWITCHES_RGB_SCREEN_70/PCB-Keyboard-EDIPO-70-MX_HOTSWAP.kicad_pcb:
v1.0.0 - © Edipo 2025
